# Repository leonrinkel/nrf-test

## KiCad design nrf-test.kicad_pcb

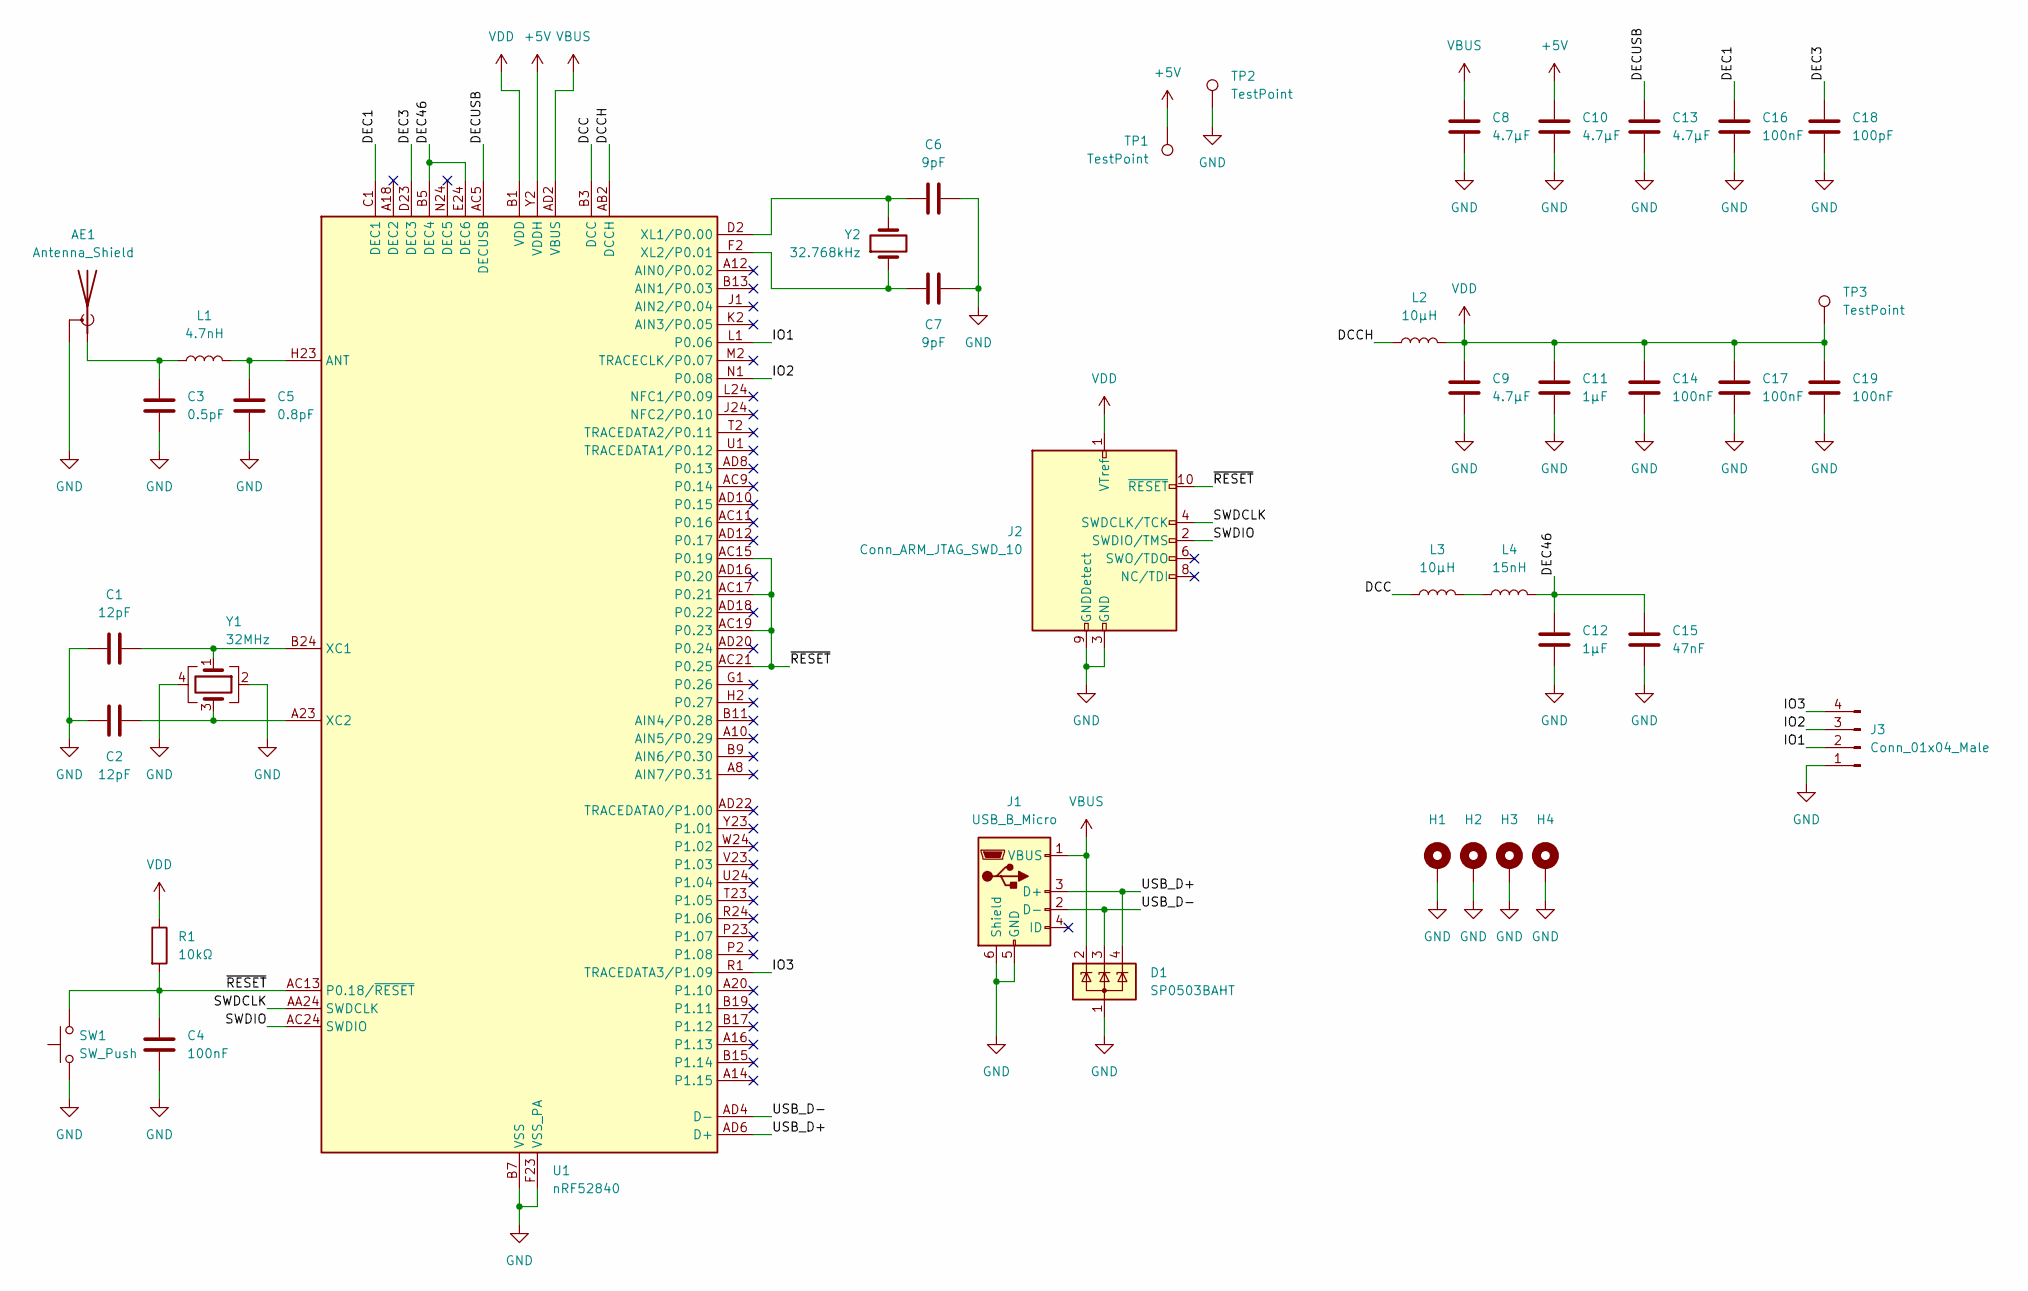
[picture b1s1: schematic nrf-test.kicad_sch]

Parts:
AE1: Antenna_Shield; Texas_SWRA117D_2.4GHz_Right
C1, C2: 12pF; C_0402_1005Metric
C3: 0.5pF; C_0402_1005Metric
C4, C14, C16, C17, C19: 100nF; C_0402_1005Metric
C5: 0.8pF; C_0402_1005Metric
C6, C7: 9pF; C_0402_1005Metric
C8, C9, C10, C13: 4.7µF; C_0603_1608Metric
C11, C12: 1µF; C_0603_1608Metric
C15: 47nF; C_0402_1005Metric
C18: 100pF; C_0402_1005Metric
D1: SP0503BAHT; SOT-143
H1, H2, H3, H4: MountingHole_Pad; MountingHole_2.2mm_M2_Pad
J1: USB_B_Micro; USB_Micro-B_Molex_47346-0001
J2: Conn_ARM_JTAG_SWD_10; PinHeader_2x05_P1.27mm_Vertical
J3: Conn_01x04_Male; PinHeader_1x04_P2.54mm_Vertical
L1: 4.7nH; L_0402_1005Metric
L2, L3: 10µH; L_0603_1608Metric
L4: 15nH; L_0402_1005Metric
R1: 10kΩ; R_0402_1005Metric
SW1: SW_Push; SW_SPST_B3U-1000P
TP1, TP2, TP3: TestPoint; TestPoint_Keystone_5005-5009_Compact
U1: nRF52840; Nordic_AQFN-73-1EP_7x7mm_P0.5mm
Y1: 32MHz; Crystal_SMD_2016-4Pin_2.0x1.6mm
Y2: 32.768kHz; Crystal_SMD_3215-2Pin_3.2x1.5mm

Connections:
+5V: C10.1, TP1.1, U1.Y2 (VDDH)
/DCC: L3.1, U1.B3 (DCC)
/DCCH: L2.1, U1.AB2 (DCCH)
/DEC1: C16.1, U1.C1 (DEC1)
/DEC3: C18.1, U1.D23 (DEC3)
/DEC46: C12.1, C15.1, L4.2, U1.B5 (DEC4), U1.E24 (DEC6)
/DECUSB: C13.1, U1.AC5 (DECUSB)
/IO1: J3.2, U1.L1 (P0.06)
/IO2: J3.3, U1.N1 (P0.08)
/IO3: J3.4, U1.R1 (TRACEDATA3/P1.09)
/SWDCLK: J2.4 (SWDCLK/TCK), U1.AA24 (SWDCLK)
/SWDIO: J2.2 (SWDIO/TMS), U1.AC24 (SWDIO)
/USB_D+: D1.4 (K), J1.3 (D+), U1.AD6 (D+)
/USB_D-: D1.3 (K), J1.2 (D-), U1.AD4 (D-)
/~RESET: C4.1, J2.10 (~RESET), R1.2, SW1.2, U1.AC13 (P0.18/~RESET), U1.AC15 (P0.19), U1.AC17 (P0.21), U1.AC19 (P0.23), U1.AC21 (P0.25)
GND: AE1.2 (Shield), C1.1, C2.1, C3.2, C4.2, C5.2, C6.2, C7.2, C8.2, C9.2, C10.2, C11.2, C12.2, C13.2, C14.2, C15.2, C16.2, C17.2, C18.2, C19.2, D1.1 (A), H1.1, H2.1, H3.1, H4.1, J1.5 (GND), J1.6 (Shield), J2.3 (GND), J2.5 (GND), J2.9 (GNDDetect), J3.1, SW1.1, TP2.1, U1.B7 (VSS), U1.EP (VSS), U1.F23 (VSS_PA), Y1.2, Y1.4
unnamed: AE1.1 (A), C3.1, L1.1
unnamed: C1.2, U1.B24 (XC1), Y1.1
unnamed: C2.2, U1.A23 (XC2), Y1.3
unnamed: C5.1, L1.2, U1.H23 (ANT)
unnamed: C6.1, U1.D2 (XL1/P0.00), Y2.2
unnamed: C7.1, U1.F2 (XL2/P0.01), Y2.1
unnamed: L3.2, L4.1
VBUS: C8.1, D1.2 (K), J1.1 (VBUS), U1.AD2 (VBUS)
VDD: C9.1, C11.1, C14.1, C17.1, C19.1, J2.1 (VTref), L2.2, R1.1, TP3.1, U1.A22 (VDD), U1.AD14 (VDD), U1.AD23 (VDD), U1.B1 (VDD), U1.W1 (VDD)

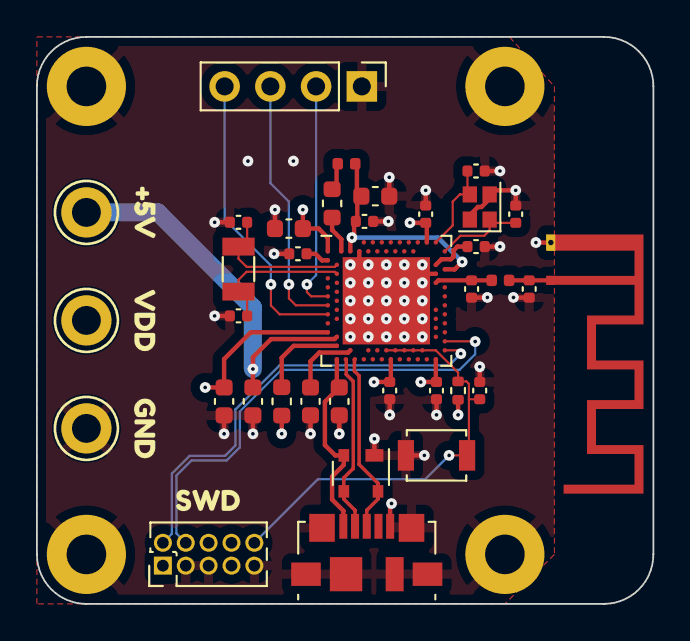
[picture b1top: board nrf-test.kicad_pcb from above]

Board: 4 copper layers, 34.2 x 31.5 mm, 44 parts (0 on the bottom side), 25 nets.

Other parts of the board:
kibuzzard-646267F1: G***; kibuzzard-646267F1
kibuzzard-646267FA: G***; kibuzzard-646267FA
kibuzzard-64626832: G***; kibuzzard-64626832
kibuzzard-64626894: G***; kibuzzard-64626894

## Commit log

2023-05-25 pick parts and add bom
